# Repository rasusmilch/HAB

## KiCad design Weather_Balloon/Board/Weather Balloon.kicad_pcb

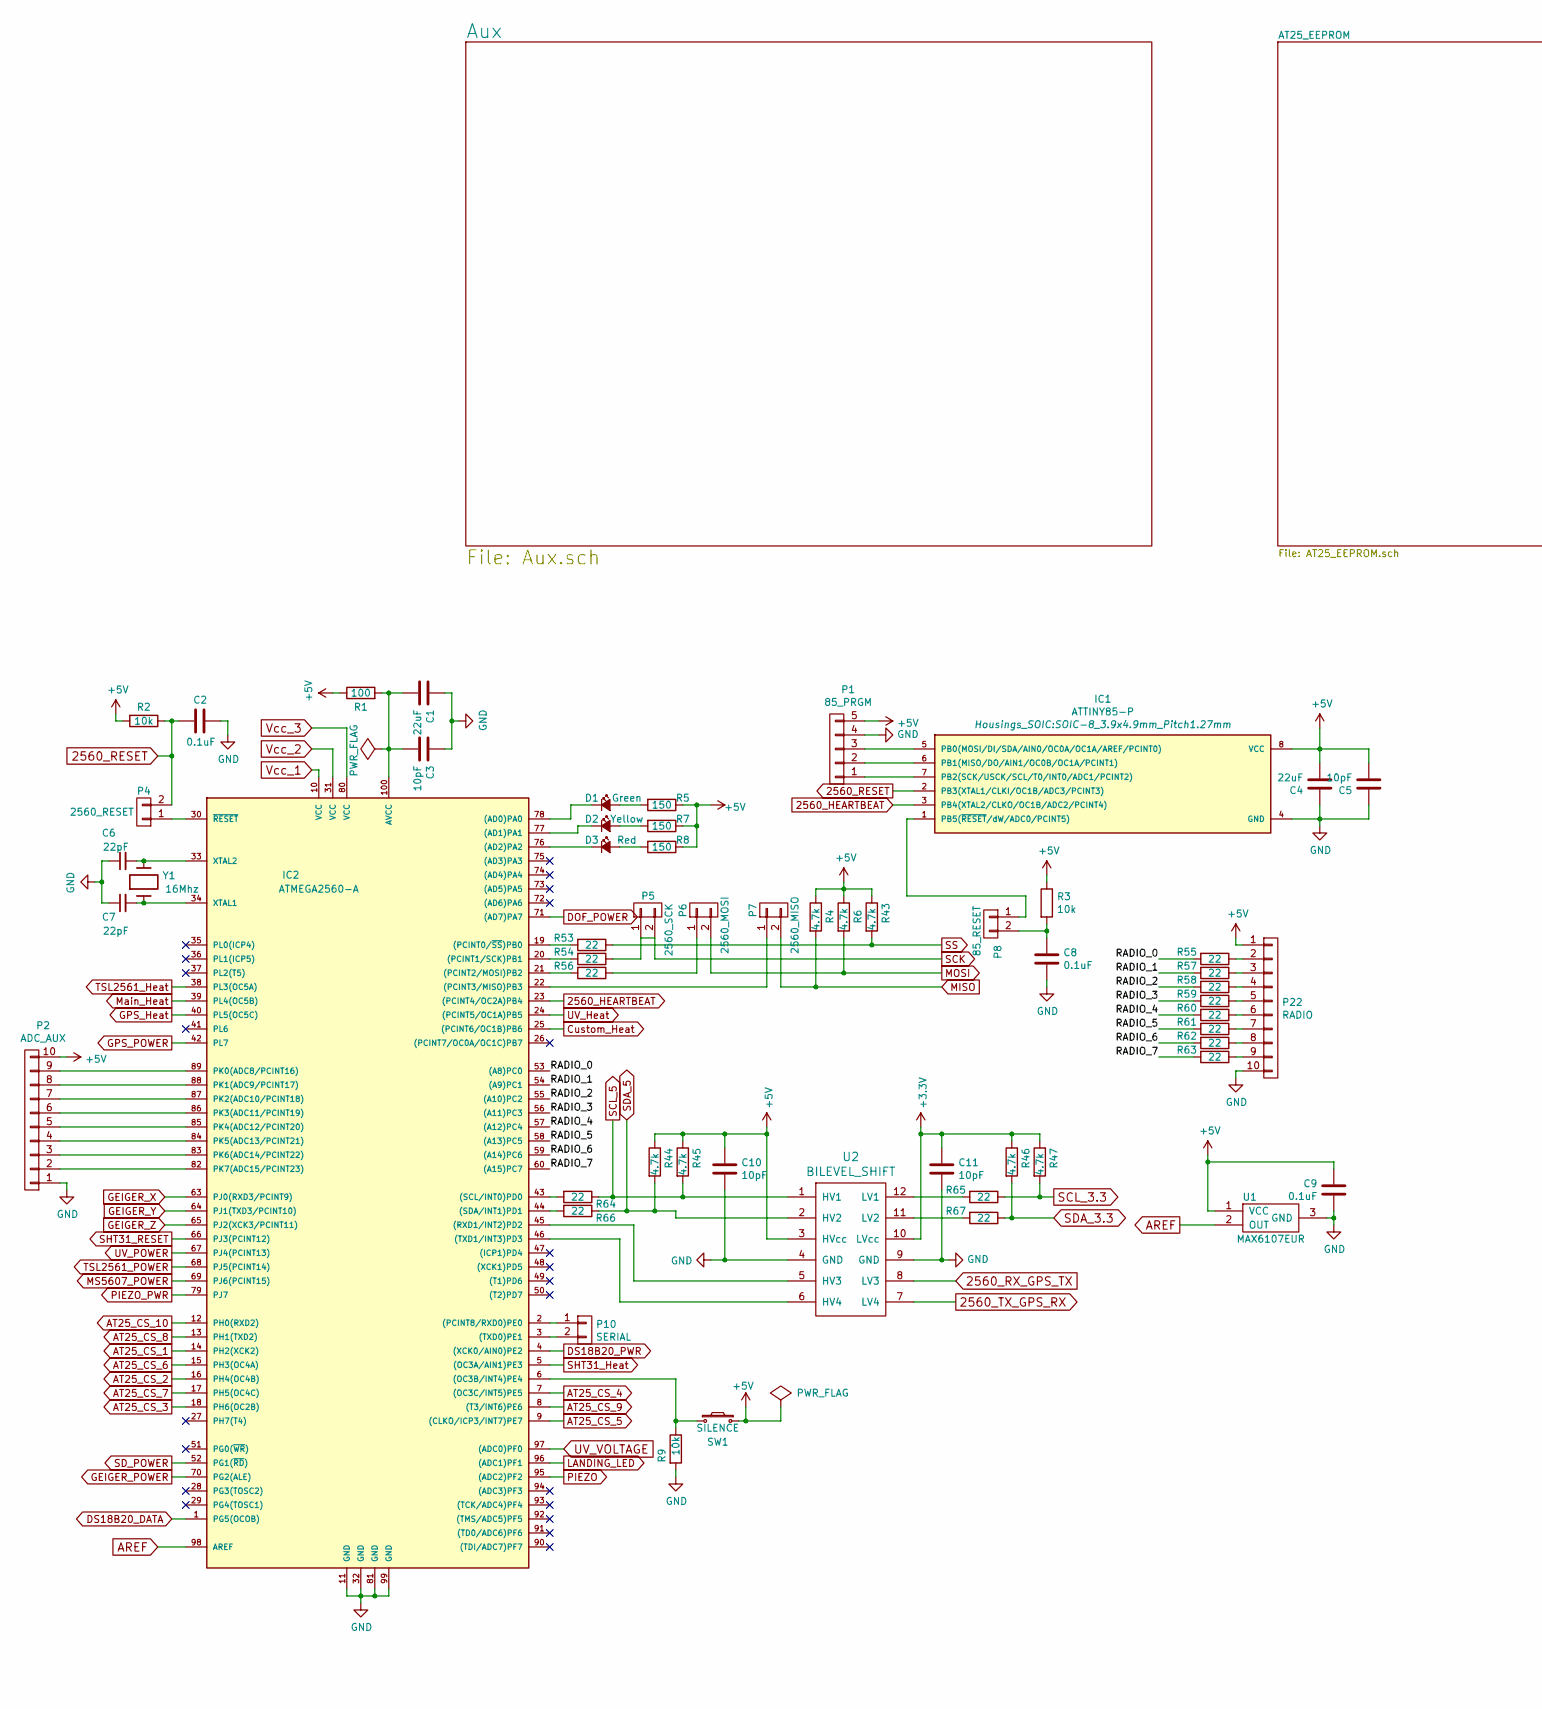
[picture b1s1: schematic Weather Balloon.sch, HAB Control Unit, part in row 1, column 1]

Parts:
C1, C4: 22uF; TantalC_SizeC_EIA-6032_HandSoldering
C2, C8, C9: 0.1uF; C_1206_HandSoldering
C3, C5, C10, C11: 10pF; C_1206_HandSoldering
C6, C7: 22pF; C_Disc_D3_P2.5
D1: Green; LED_1206
D2: Yellow; LED_1206
D3: Red; LED_1206
IC1: ATTINY85-P; SOIC-8_3.9x4.9mm_Pitch1.27mm
IC2: ATMEGA2560-A; TQFP-100_14x14mm_Pitch0.5mm
P1: 85_PRGM; Pin_Header_Straight_1x05
P2: ADC_AUX; Pin_Header_Straight_1x10
P4: 2560_RESET; Pin_Header_Straight_1x02
P5: 2560_SCK; Pin_Header_Straight_1x02
P6: 2560_MOSI; Pin_Header_Straight_1x02
P7: 2560_MISO; Pin_Header_Straight_1x02
P8: 85_RESET; Pin_Header_Straight_1x02
P10: SERIAL; Pin_Header_Straight_1x02
P22: RADIO; Pin_Header_Straight_1x10
R1: 100; R_1206_HandSoldering
R2, R3, R9: 10k; R_1206_HandSoldering
R4, R6, R43, R44, R45, R46, R47: 4.7k; R_1206_HandSoldering
R5, R7, R8: 150; R_1206_HandSoldering
R53, R54, R55, R56, R57, R58, R59, R60, R61, R62, R63, R64, R65, R66, R67: 22; R_1206_HandSoldering
SW1: SILENCE; SW_PUSH_6mm
U1: MAX6107EUR; SOT-23_Handsoldering
U2: BILEVEL_SHIFT; DIP-12_W7.62mm_LongPads_ALL
Y1: 16Mhz; HC-49V

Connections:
2560_HEARTBEAT: IC1.3 (PB4(XTAL2/CLKO/OC1B/ADC2/PCINT4)), IC2.23 ((PCINT4/OC2A)PB4)
2560_RESET: C2.2, IC1.2 (PB3(XTAL1/CLKI/OC1B/ADC3/PCINT3)), P4.2, R2.1
2560_RX_GPS_TX: U2.8 (LV3); also elsewhere on the board
2560_TX_GPS_RX: U2.7 (LV4); also elsewhere on the board
+3V3: C11.1, R46.1, R47.1, U2.10 (LVcc); also elsewhere on the board
/RADIO_0: IC2.53 ((A8)PC0), R55.2
/RADIO_1: IC2.54 ((A9)PC1), R57.2
/RADIO_2: IC2.55 ((A10)PC2), R58.2
/RADIO_3: IC2.56 ((A11)PC3), R59.2
/RADIO_4: IC2.57 ((A12)PC4), R60.2
/RADIO_5: IC2.58 ((A13)PC5), R61.2
/RADIO_6: IC2.59 ((A14)PC6), R62.2
/RADIO_7: IC2.60 ((A15)PC7), R63.2
AREF: IC2.98 (AREF), U1.2 (OUT)
AT25_CS_1: IC2.14 (PH2(XCK2)); also elsewhere on the board
AT25_CS_2: IC2.16 (PH4(OC4B)); also elsewhere on the board
AT25_CS_3: IC2.18 (PH6(OC2B)); also elsewhere on the board
AT25_CS_4: IC2.7 ((OC3C/INT5)PE5); also elsewhere on the board
AT25_CS_5: IC2.9 ((CLKO/ICP3/INT7)PE7); also elsewhere on the board
AT25_CS_6: IC2.15 (PH3(OC4A)); also elsewhere on the board
AT25_CS_7: IC2.17 (PH5(OC4C)); also elsewhere on the board
AT25_CS_8: IC2.13 (PH1(TXD2)); also elsewhere on the board
AT25_CS_9: IC2.8 ((T3/INT6)PE6); also elsewhere on the board
AT25_CS_10: IC2.12 (PH0(RXD2)); also elsewhere on the board
Custom_Heat: IC2.25 ((PCINT6/OC1B)PB6); also elsewhere on the board
DOF_POWER: IC2.71 ((AD7)PA7); also elsewhere on the board
DS18B20_DATA: IC2.1 (PG5(OCOB)); also elsewhere on the board
DS18B20_PWR: IC2.4 ((XCK0/AIN0)PE2); also elsewhere on the board
GEIGER_POWER: IC2.70 (PG2(ALE)); also elsewhere on the board
GEIGER_X: IC2.63 (PJ0(RXD3/PCINT9)); also elsewhere on the board
GEIGER_Y: IC2.64 (PJ1(TXD3/PCINT10)); also elsewhere on the board
GEIGER_Z: IC2.65 (PJ2(XCK3/PCINT11)); also elsewhere on the board
GND: C1.1, C2.1, C3.1, C4.1, C5.1, C6.1, C7.1, C8.2, C9.2, C10.2, C11.2, IC1.4 (GND), IC2.11 (GND), IC2.32 (GND), IC2.81 (GND), IC2.99 (GND), P1.4, P2.1, P22.10, R9.2, U1.3 (GND), U2.4 (GND), U2.9 (GND); also elsewhere on the board
GPS_Heat: IC2.40 (PL5(OC5C)); also elsewhere on the board
GPS_POWER: IC2.42 (PL7); also elsewhere on the board
LANDING_LED: IC2.96 ((ADC1)PF1); also elsewhere on the board
MISO: P7.2, R4.2; also elsewhere on the board
MOSI: P6.2, R6.2; also elsewhere on the board
MS5607_POWER: IC2.69 (PJ6(PCINT15)); also elsewhere on the board
Main_Heat: IC2.39 (PL4(OC5B)); also elsewhere on the board
unnamed: C1.2, C3.2, IC2.100 (AVCC), R1.2
unnamed: C6.2, IC2.33 (XTAL2), Y1.2
unnamed: C7.2, IC2.34 (XTAL1), Y1.1
unnamed: C8.1, P8.2, R3.2
unnamed: D1.1 (K), IC2.78 ((AD0)PA0)
unnamed: D1.2 (A), R5.2
unnamed: D2.1 (K), IC2.77 ((AD1)PA1)
unnamed: D2.2 (A), R7.2
unnamed: D3.1 (K), IC2.76 ((AD2)PA2)
unnamed: D3.2 (A), R8.2
unnamed: IC1.1 (PB5(~RESET~/dW/ADC0/PCINT5)), P8.1
unnamed: IC1.5 (PB0(MOSI/DI/SDA/AIN0/OC0A/OC1A/AREF/PCI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), P1.3
unnamed: IC1.6 (PB1(MISO/DO/AIN1/OC0B/OC1A/PCINT1)), P1.2
unnamed: IC1.7 (PB2(SCK/USCK/SCL/T0/INT0/ADC1/PCINT2)), P1.1
unnamed: IC2.2 ((PCINT8/RXD0)PE0), P10.1
unnamed: IC2.3 ((TXD0)PE1), P10.2
unnamed: IC2.6 ((OC3B/INT4)PE4), R9.1, SW1.1
unnamed: IC2.19 ((PCINT0/~SS~)PB0), R53.2
unnamed: IC2.20 ((PCINT1/SCK)PB1), R54.2
unnamed: IC2.21 ((PCINT2/MOSI)PB2), R56.2
unnamed: IC2.22 ((PCINT3/MISO)PB3), P7.1
unnamed: IC2.30 (~RESET), P4.1
unnamed: IC2.43 ((SCL/INT0)PD0), R64.2
unnamed: IC2.44 ((SDA/INT1)PD1), R66.2
unnamed: IC2.45 ((RXD1/INT2)PD2), U2.5 (HV3)
unnamed: IC2.46 ((TXD1/INT3)PD3), U2.6 (HV4)
unnamed: IC2.82 (PK7(ADC15/PCINT23)), P2.2
unnamed: IC2.83 (PK6(ADC14/PCINT22)), P2.3
unnamed: IC2.84 (PK5(ADC13/PCINT21)), P2.4
unnamed: IC2.85 (PK4(ADC12/PCINT20)), P2.5
unnamed: IC2.86 (PK3(ADC11/PCINT19)), P2.6
unnamed: IC2.87 (PK2(ADC10/PCINT18)), P2.7
unnamed: IC2.88 (PK1(ADC9/PCINT17)), P2.8
unnamed: IC2.89 (PK0(ADC8/PCINT16)), P2.9
unnamed: P6.1, R56.1
unnamed: P22.2, R55.1
unnamed: P22.3, R57.1
unnamed: P22.4, R58.1
unnamed: P22.5, R59.1
unnamed: P22.6, R60.1
unnamed: P22.7, R61.1
unnamed: P22.8, R62.1
unnamed: P22.9, R63.1
unnamed: R65.2, U2.12 (LV1)
unnamed: R67.2, U2.11 (LV2)
PIEZO: IC2.95 ((ADC2)PF2); also elsewhere on the board
PIEZO_PWR: IC2.79 (PJ7); also elsewhere on the board
SCK: P5.1, P5.2, R54.1; also elsewhere on the board
SCL_3.3: R47.2, R65.1; also elsewhere on the board
SCL_5: R45.2, R64.1, U2.1 (HV1); also elsewhere on the board
SDA_3.3: R46.2, R67.1; also elsewhere on the board
SDA_5: R44.2, R66.1, U2.2 (HV2); also elsewhere on the board
SD_POWER: IC2.52 (PG1(~RD~)); also elsewhere on the board
SHT31_Heat: IC2.5 ((OC3A/AIN1)PE3); also elsewhere on the board
SHT31_RESET: IC2.66 (PJ3(PCINT12)); also elsewhere on the board
SS: R43.2, R53.1; also elsewhere on the board
TSL2561_Heat: IC2.38 (PL3(OC5A)); also elsewhere on the board
TSL2561_POWER: IC2.68 (PJ5(PCINT14)); also elsewhere on the board
UV_Heat: IC2.24 ((PCINT5/OC1A)PB5); also elsewhere on the board
UV_POWER: IC2.67 (PJ4(PCINT13)); also elsewhere on the board
UV_VOLTAGE: IC2.97 ((ADC0)PF0); also elsewhere on the board
Vcc_1: C4.2, C5.2, C9.1, C10.1, IC1.8 (VCC), IC2.10 (VCC), IC2.31 (VCC), IC2.80 (VCC), P1.5, P2.10, P22.1, R1.1, R2.2, R3.1, R4.1, R5.1, R6.1, R7.1, R8.1, R43.1, R44.1, R45.1, SW1.2, U1.1 (VCC), U2.3 (HVcc); also elsewhere on the board

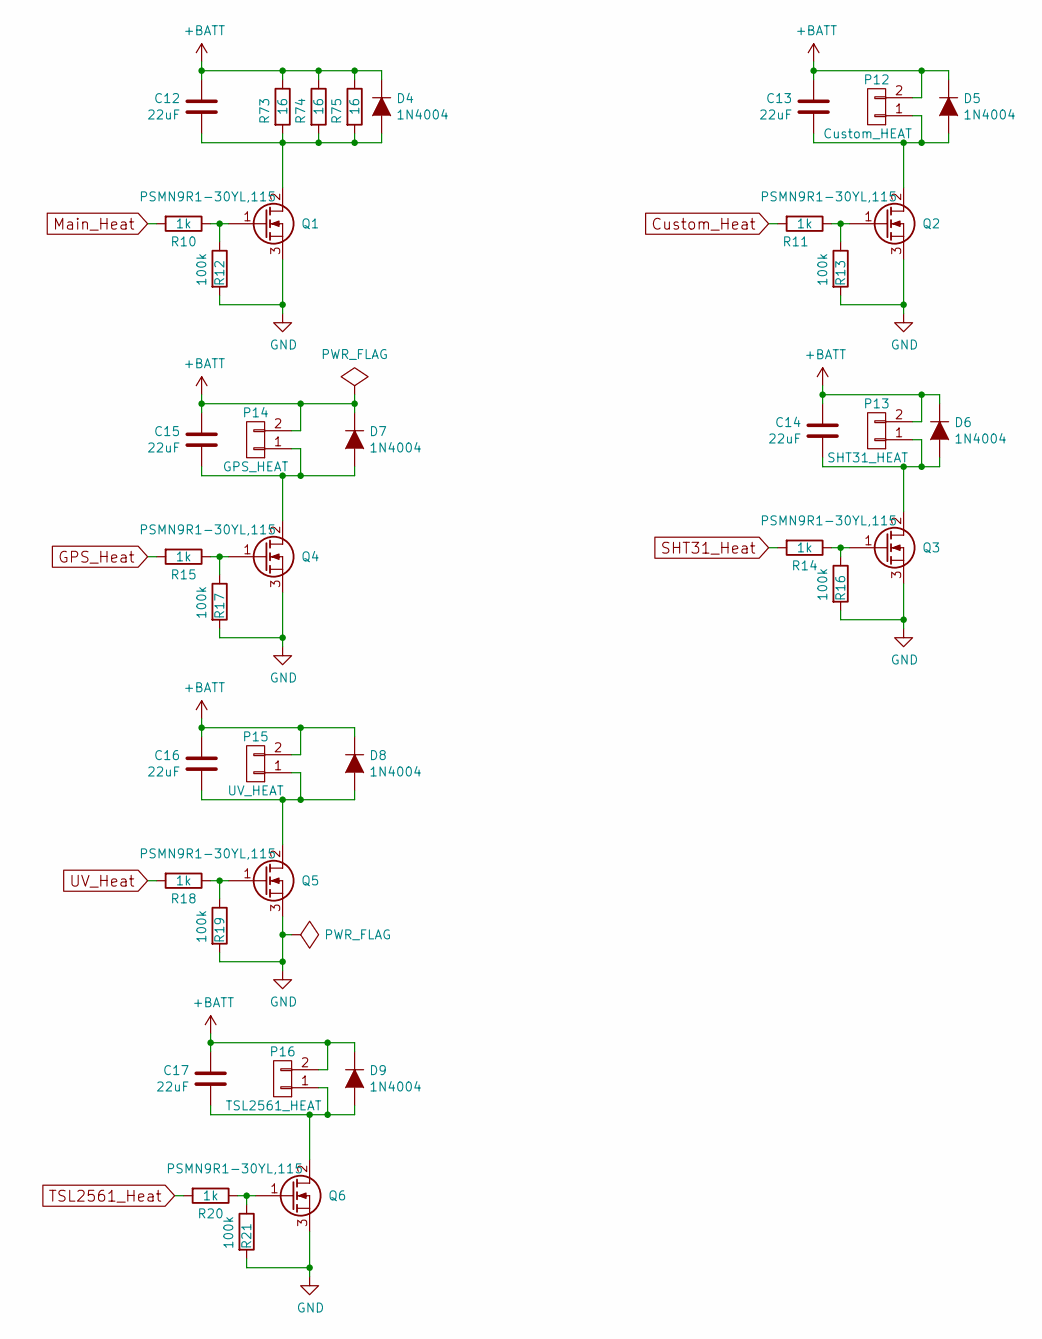
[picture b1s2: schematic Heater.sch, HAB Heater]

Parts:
C12, C13, C14, C15, C16, C17: 22uF; TantalC_SizeC_EIA-6032_HandSoldering
D4, D5, D6, D7, D8, D9: 1N4004; SMA_Handsoldering
P12: Custom_HEAT; Pin_Header_Straight_1x02
P13: SHT31_HEAT; Pin_Header_Straight_1x02
P14: GPS_HEAT; Pin_Header_Straight_1x02
P15: UV_HEAT; Pin_Header_Straight_1x02
P16: TSL2561_HEAT; Pin_Header_Straight_1x02
Q1, Q2, Q3, Q4, Q5, Q6: PSMN9R1-30YL,115; SOT-669_LFPAK
R10, R11, R14, R15, R18, R20: 1k; R_1206_HandSoldering
R12, R13, R16, R17, R19, R21: 100k; R_1206_HandSoldering
R73, R74, R75: 16; R_1206_WIDE

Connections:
+BATT: C12.1, C13.1, C14.1, C15.1, C16.1, C17.1, D4.1 (K), D5.1 (K), D6.1 (K), D7.1 (K), D8.1 (K), D9.1 (K), P12.2, P13.2, P14.2, P15.2, P16.2, R73.1, R74.1, R75.1; also elsewhere on the board
Custom_Heat: R11.2; also elsewhere on the board
GND: Q1.3 (S), Q2.3 (S), Q3.3 (S), Q4.3 (S), Q5.3 (S), Q6.3 (S), R12.2, R13.2, R16.2, R17.2, R19.2, R21.2; also elsewhere on the board
GPS_Heat: R15.2; also elsewhere on the board
Main_Heat: R10.2; also elsewhere on the board
unnamed: C12.2, D4.2 (A), Q1.2 (D), R73.2, R74.2, R75.2
unnamed: C13.2, D5.2 (A), P12.1, Q2.2 (D)
unnamed: C14.2, D6.2 (A), P13.1, Q3.2 (D)
unnamed: C15.2, D7.2 (A), P14.1, Q4.2 (D)
unnamed: C16.2, D8.2 (A), P15.1, Q5.2 (D)
unnamed: C17.2, D9.2 (A), P16.1, Q6.2 (D)
unnamed: Q1.1 (G), R10.1, R12.1
unnamed: Q2.1 (G), R11.1, R13.1
unnamed: Q3.1 (G), R14.1, R16.1
unnamed: Q4.1 (G), R15.1, R17.1
unnamed: Q5.1 (G), R18.1, R19.1
unnamed: Q6.1 (G), R20.1, R21.1
SHT31_Heat: R14.2; also elsewhere on the board
TSL2561_Heat: R20.2; also elsewhere on the board
UV_Heat: R18.2; also elsewhere on the board

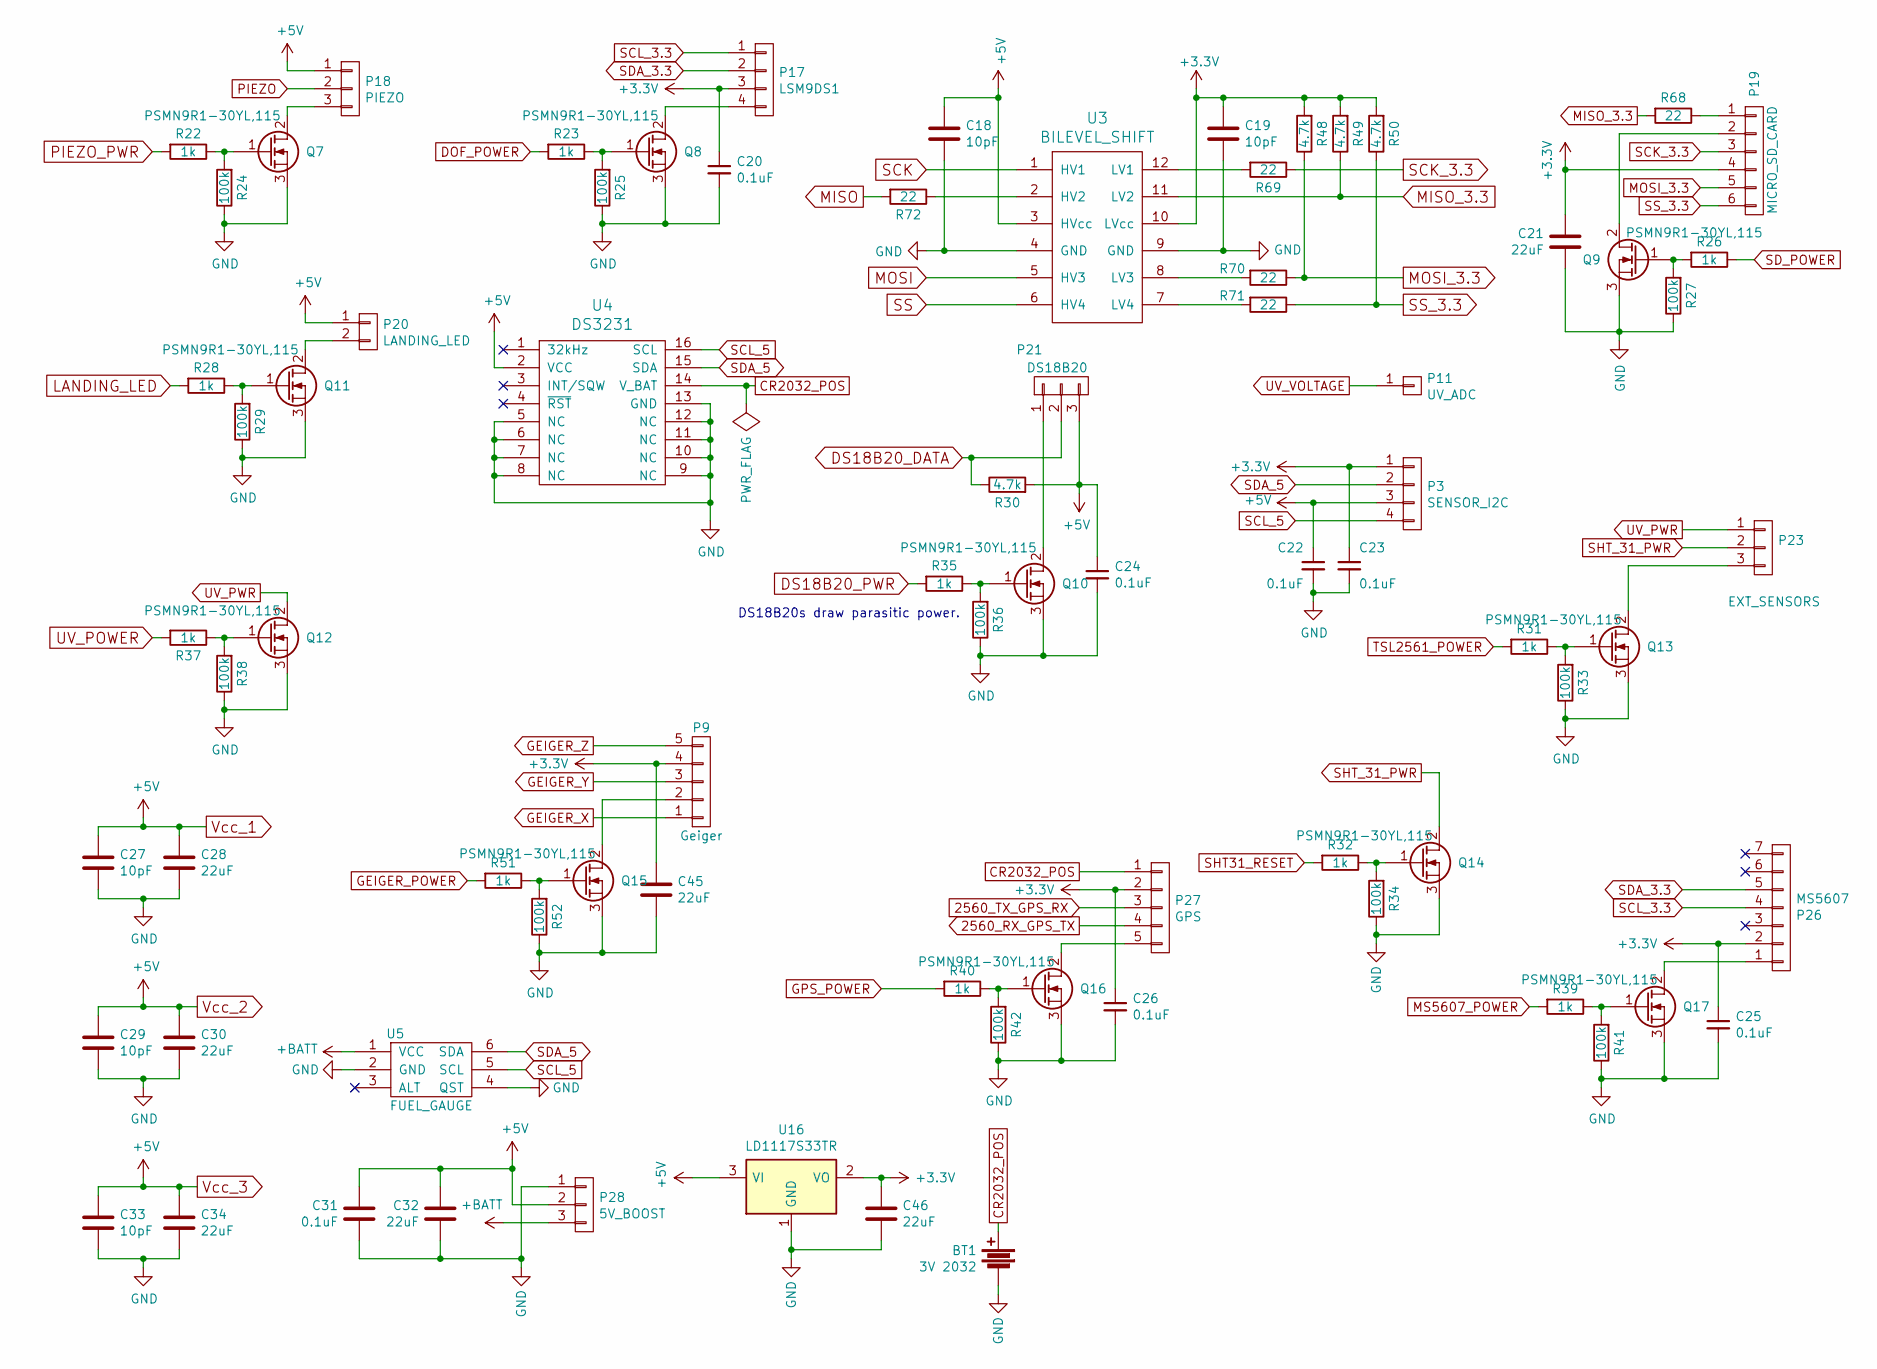
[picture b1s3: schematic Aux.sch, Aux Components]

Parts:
BT1: 3V 2032; CR2032
C18, C19, C27, C29, C33: 10pF; C_1206_HandSoldering
C20, C22, C23, C24, C25, C26, C31: 0.1uF; C_1206_HandSoldering
C21, C32, C34, C45, C46: 22uF; C_1206_HandSoldering
C28, C30: 22uF; TantalC_SizeC_EIA-6032_HandSoldering
P3: SENSOR_I2C; Pin_Header_Straight_1x04
P9: Geiger; Pin_Header_Straight_1x05
P11: UV_ADC; Pin_Header_Straight_1x01
P17: LSM9DS1; LSM9DS1_ALL
P18: PIEZO; Pin_Header_Straight_1x03
P19: MICRO_SD_CARD; MicroSD_ALL
P20: LANDING_LED; Pin_Header_Straight_1x02
P21: DS18B20; Pin_Header_Straight_1x03
P23: EXT_SENSORS; Pin_Header_Straight_1x03
P26: MS5607; MS5607_ALL
P27: GPS; Pin_Header_Straight_1x05
P28: 5V_BOOST; Voltage_Booster_ALL
Q7, Q8, Q9, Q10, Q11, Q12, Q13, Q14, Q15, Q16, Q17: PSMN9R1-30YL,115; SOT-669_LFPAK
R22, R23, R26, R28, R31, R32, R35, R37, R39, R40, R51: 1k; R_1206_HandSoldering
R24, R25, R27, R29, R33, R34, R36, R38, R41, R42, R52: 100k; R_1206_HandSoldering
R30, R48, R49, R50: 4.7k; R_1206_HandSoldering
R68, R69, R70, R71, R72: 22; R_1206_HandSoldering
U3: BILEVEL_SHIFT; DIP-12_W7.62mm_LongPads_ALL
U4: DS3231; SO-16-W
U5: FUEL_GAUGE; FUEL_GAUGE_ALL
U16: LD1117S33TR; TO-220

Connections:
2560_RX_GPS_TX: P27.4; also elsewhere on the board
2560_TX_GPS_RX: P27.3; also elsewhere on the board
+3V3: C19.1, C20.1, C21.1, C23.1, C25.1, C26.1, C45.2, C46.2, P3.1, P9.4, P17.3, P19.4, P26.2, P27.2, R48.2, R49.2, R50.2, U3.10 (LVcc), U16.2 (VO); also elsewhere on the board
+BATT: P28.3, U5.1 (VCC); also elsewhere on the board
CR2032_POS: BT1.1, P27.1, U4.14 (V_BAT)
DOF_POWER: R23.2; also elsewhere on the board
DS18B20_DATA: P21.2, R30.1; also elsewhere on the board
DS18B20_PWR: R35.2; also elsewhere on the board
GEIGER_POWER: R51.2; also elsewhere on the board
GEIGER_X: P9.1; also elsewhere on the board
GEIGER_Y: P9.3; also elsewhere on the board
GEIGER_Z: P9.5; also elsewhere on the board
GND: BT1.2, C18.2, C19.2, C20.2, C21.2, C22.2, C23.2, C24.2, C25.2, C26.2, C27.2, C28.2, C29.2, C30.2, C31.1, C32.1, C33.2, C34.2, C45.1, C46.1, P28.1, Q7.3 (S), Q8.3 (S), Q9.3 (S), Q10.3 (S), Q11.3 (S), Q12.3 (S), Q13.3 (S), Q14.3 (S), Q15.3 (S), Q16.3 (S), Q17.3 (S), R24.1, R25.1, R27.1, R29.1, R33.1, R34.1, R36.1, R38.1, R41.1, R42.1, R52.1, U3.4 (GND), U3.9 (GND), U4.5 (NC), U4.6 (NC), U4.7 (NC), U4.8 (NC), U4.9 (NC), U4.10 (NC), U4.11 (NC), U4.12 (NC), U4.13 (GND), U5.2 (GND), U5.4 (QST), U16.1 (GND); also elsewhere on the board
GPS_POWER: R40.2; also elsewhere on the board
LANDING_LED: R28.2; also elsewhere on the board
MISO: R72.2; also elsewhere on the board
MISO_3.3: R49.1, R68.2, U3.11 (LV2)
MOSI: U3.5 (HV3); also elsewhere on the board
MOSI_3.3: P19.5, R48.1, R70.1
MS5607_POWER: R39.2; also elsewhere on the board
unnamed: P9.2, Q15.2 (D)
unnamed: P17.4, Q8.2 (D)
unnamed: P18.3, Q7.2 (D)
unnamed: P19.1, R68.1
unnamed: P19.2, Q9.2 (D)
unnamed: P20.2, Q11.2 (D)
unnamed: P21.1, Q10.2 (D)
unnamed: P23.3, Q13.2 (D)
unnamed: P26.1, Q17.2 (D)
unnamed: P27.5, Q16.2 (D)
unnamed: Q7.1 (G), R22.1, R24.2
unnamed: Q8.1 (G), R23.1, R25.2
unnamed: Q9.1 (G), R26.2, R27.2
unnamed: Q10.1 (G), R35.1, R36.2
unnamed: Q11.1 (G), R28.1, R29.2
unnamed: Q12.1 (G), R37.1, R38.2
unnamed: Q13.1 (G), R31.1, R33.2
unnamed: Q14.1 (G), R32.1, R34.2
unnamed: Q15.1 (G), R51.1, R52.2
unnamed: Q16.1 (G), R40.1, R42.2
unnamed: Q17.1 (G), R39.1, R41.2
unnamed: R69.2, U3.12 (LV1)
unnamed: R70.2, U3.8 (LV3)
unnamed: R71.2, U3.7 (LV4)
unnamed: R72.1, U3.2 (HV2)
PIEZO: P18.2; also elsewhere on the board
PIEZO_PWR: R22.2; also elsewhere on the board
SCK: U3.1 (HV1); also elsewhere on the board
SCK_3.3: P19.3, R69.1
SCL_3.3: P17.1, P26.4; also elsewhere on the board
SCL_5: P3.4, U4.16 (SCL), U5.5 (SCL); also elsewhere on the board
SDA_3.3: P17.2, P26.5; also elsewhere on the board
SDA_5: P3.2, U4.15 (SDA), U5.6 (SDA); also elsewhere on the board
SD_POWER: R26.1; also elsewhere on the board
SHT31_RESET: R32.2; also elsewhere on the board
SHT_31_PWR: P23.2, Q14.2 (D)
SS: U3.6 (HV4); also elsewhere on the board
SS_3.3: P19.6, R50.1, R71.1
TSL2561_POWER: R31.2; also elsewhere on the board
UV_POWER: R37.2; also elsewhere on the board
UV_PWR: P23.1, Q12.2 (D)
UV_VOLTAGE: P11.1; also elsewhere on the board
Vcc_1: C18.1, C22.1, C24.1, C27.1, C28.1, C29.1, C30.1, C31.2, C32.2, C33.1, C34.1, P3.3, P18.1, P20.1, P21.3, P28.2, R30.2, U3.3 (HVcc), U4.2 (VCC), U16.3 (VI); also elsewhere on the board

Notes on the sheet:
DS18B20s draw parasitic power.

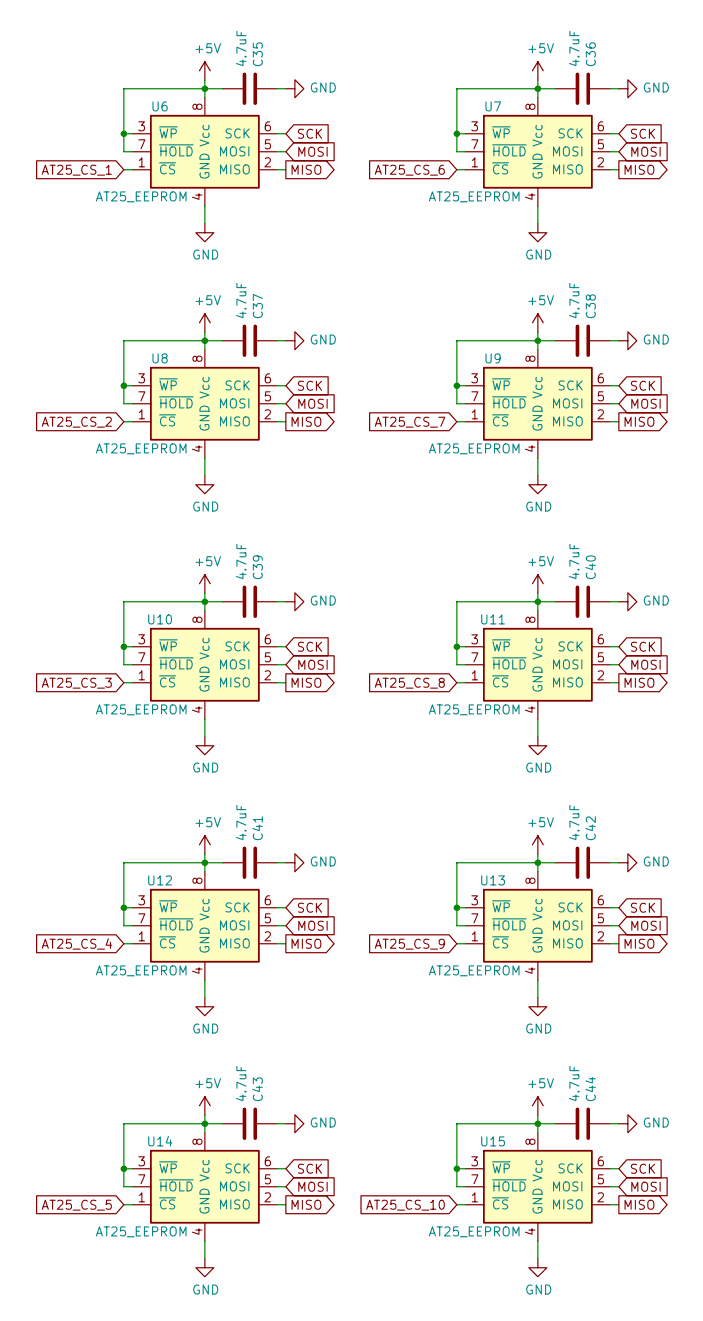
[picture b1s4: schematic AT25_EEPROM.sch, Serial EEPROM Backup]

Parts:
C35, C36, C37, C38, C39, C40, C41, C42, C43, C44: 4.7uF; C_0603_HandSoldering
U6, U7, U8, U9, U10, U11, U12, U13, U14, U15: AT25_EEPROM; SOIC-8_3.9x4.9mm_Pitch1.27mm

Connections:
AT25_CS_1: U6.1 (~CS); also elsewhere on the board
AT25_CS_2: U8.1 (~CS); also elsewhere on the board
AT25_CS_3: U10.1 (~CS); also elsewhere on the board
AT25_CS_4: U12.1 (~CS); also elsewhere on the board
AT25_CS_5: U14.1 (~CS); also elsewhere on the board
AT25_CS_6: U7.1 (~CS); also elsewhere on the board
AT25_CS_7: U9.1 (~CS); also elsewhere on the board
AT25_CS_8: U11.1 (~CS); also elsewhere on the board
AT25_CS_9: U13.1 (~CS); also elsewhere on the board
AT25_CS_10: U15.1 (~CS); also elsewhere on the board
GND: C35.1, C36.1, C37.1, C38.1, C39.1, C40.1, C41.1, C42.1, C43.1, C44.1, U6.4 (GND), U7.4 (GND), U8.4 (GND), U9.4 (GND), U10.4 (GND), U11.4 (GND), U12.4 (GND), U13.4 (GND), U14.4 (GND), U15.4 (GND); also elsewhere on the board
MISO: U6.2 (MISO), U7.2 (MISO), U8.2 (MISO), U9.2 (MISO), U10.2 (MISO), U11.2 (MISO), U12.2 (MISO), U13.2 (MISO), U14.2 (MISO), U15.2 (MISO); also elsewhere on the board
MOSI: U6.5 (MOSI), U7.5 (MOSI), U8.5 (MOSI), U9.5 (MOSI), U10.5 (MOSI), U11.5 (MOSI), U12.5 (MOSI), U13.5 (MOSI), U14.5 (MOSI), U15.5 (MOSI); also elsewhere on the board
SCK: U6.6 (SCK), U7.6 (SCK), U8.6 (SCK), U9.6 (SCK), U10.6 (SCK), U11.6 (SCK), U12.6 (SCK), U13.6 (SCK), U14.6 (SCK), U15.6 (SCK); also elsewhere on the board
Vcc_1: C35.2, C36.2, C37.2, C38.2, C39.2, C40.2, C41.2, C42.2, C43.2, C44.2, U6.3 (~WP), U6.7 (~HOLD), U6.8 (Vcc), U7.3 (~WP), U7.7 (~HOLD), U7.8 (Vcc), U8.3 (~WP), U8.7 (~HOLD), U8.8 (Vcc), U9.3 (~WP), U9.7 (~HOLD), U9.8 (Vcc), U10.3 (~WP), U10.7 (~HOLD), U10.8 (Vcc), U11.3 (~WP), U11.7 (~HOLD), U11.8 (Vcc), U12.3 (~WP), U12.7 (~HOLD), U12.8 (Vcc), U13.3 (~WP), U13.7 (~HOLD), U13.8 (Vcc), U14.3 (~WP), U14.7 (~HOLD), U14.8 (Vcc), U15.3 (~WP), U15.7 (~HOLD), U15.8 (Vcc); also elsewhere on the board

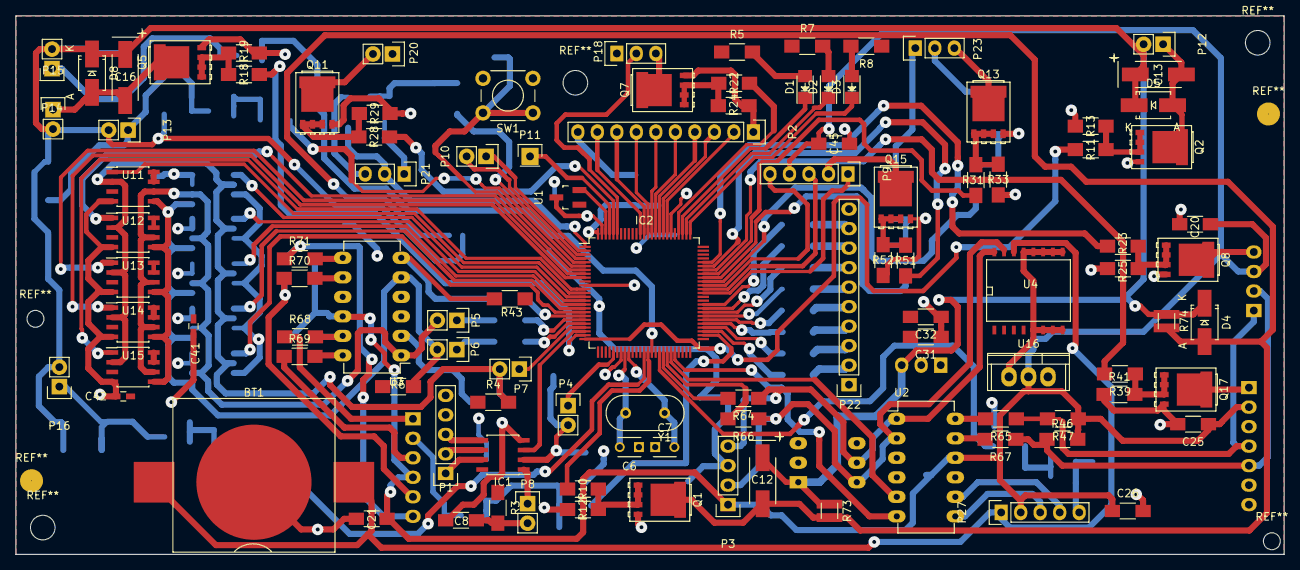
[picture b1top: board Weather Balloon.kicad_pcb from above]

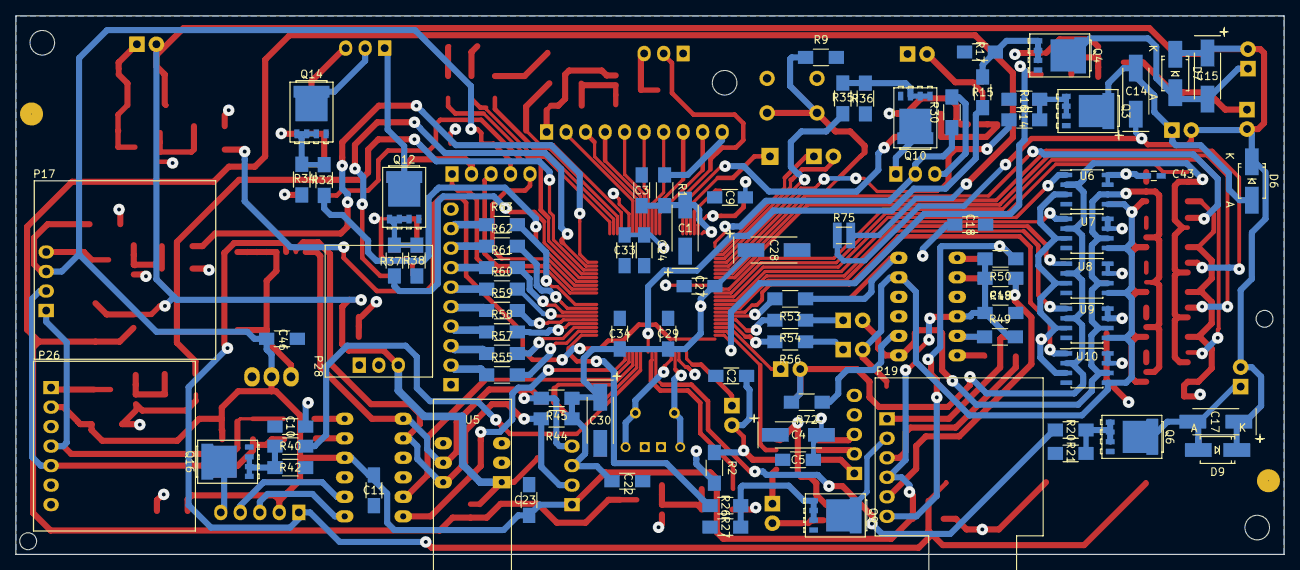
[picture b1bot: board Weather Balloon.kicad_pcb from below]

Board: 2 copper layers, 165.1 x 70.1 mm, 187 parts (83 on the bottom side), 147 nets.

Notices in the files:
Weather_Balloon/Weather_Balloon/Weather_Balloon.ino:
Licensed GPLv3
Oven Controller/Oven Controller.sch:
Copyright 2016
